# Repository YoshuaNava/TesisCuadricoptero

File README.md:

Estabilización de un cuadricoptero mediante un algoritmo Proporcional-Integral-Derivativo
==================

Documentos, códigos, imagenes y videos de la tesis. 

Trabajo realizado por Luis Vicens y Yoshua Nava, estudiantes de Ingeniería Informática de la Universidad Católica Andrés Bello.

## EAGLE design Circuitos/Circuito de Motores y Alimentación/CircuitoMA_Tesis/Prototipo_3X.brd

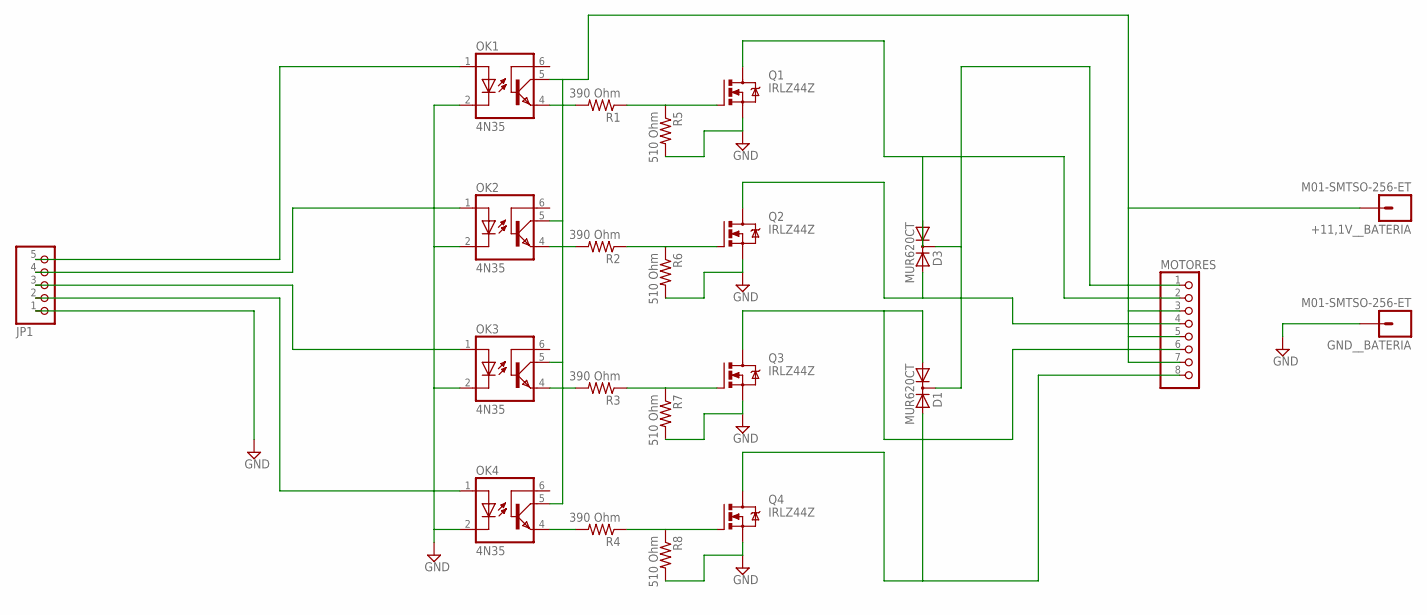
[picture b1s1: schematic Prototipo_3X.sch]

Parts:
+11,1V__BATERIA: M01-SMTSO-256-ET; SMTSO-256-ET
D1, D3: MUR620CT; TO220AB
GND__BATERIA: M01-SMTSO-256-ET; SMTSO-256-ET
JP1: PINHD-1X5/90; 1X05/90
MOTORES: PINHD-1X8/90; 1X08/90
OK1, OK2, OK3, OK4: 4N35; DIL06
Q1, Q2, Q3, Q4: IRLZ44Z; TO220BH
R1, R2, R3, R4: 390 Ohm; 0207/7
R5, R6, R7, R8: 510 Ohm; 0207/7

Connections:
GND: GND__BATERIA.P$1, JP1.1, OK1.2 (C), OK2.2 (C), OK3.2 (C), OK4.2 (C), Q1.S, Q2.S, Q3.S, Q4.S, R5.2, R6.2, R7.2, R8.2
unnamed: JP1.5, OK1.1 (A)
unnamed: JP1.4, OK2.1 (A)
unnamed: JP1.3, OK3.1 (A)
unnamed: JP1.2, OK4.1 (A)
unnamed: OK1.4 (EMI), R1.2
unnamed: Q1.G, R1.1, R5.1
unnamed: OK2.4 (EMI), R2.2
unnamed: OK3.4 (EMI), R3.2
unnamed: OK4.4 (EMI), R4.2
unnamed: Q4.G, R4.1, R8.1
unnamed: D3.A1, MOTORES.2, Q1.D
unnamed: Q3.G, R3.1, R7.1
unnamed: D3.A2, MOTORES.4, Q2.D
unnamed: D1.A1, MOTORES.6, Q3.D
unnamed: D1.A2, MOTORES.8, Q4.D
unnamed: Q2.G, R2.1, R6.1
unnamed: +11,1V__BATERIA.P$1, D1.C, D3.C, MOTORES.1, MOTORES.3, MOTORES.5, MOTORES.7, OK1.5 (COL), OK2.5 (COL), OK3.5 (COL), OK4.5 (COL)

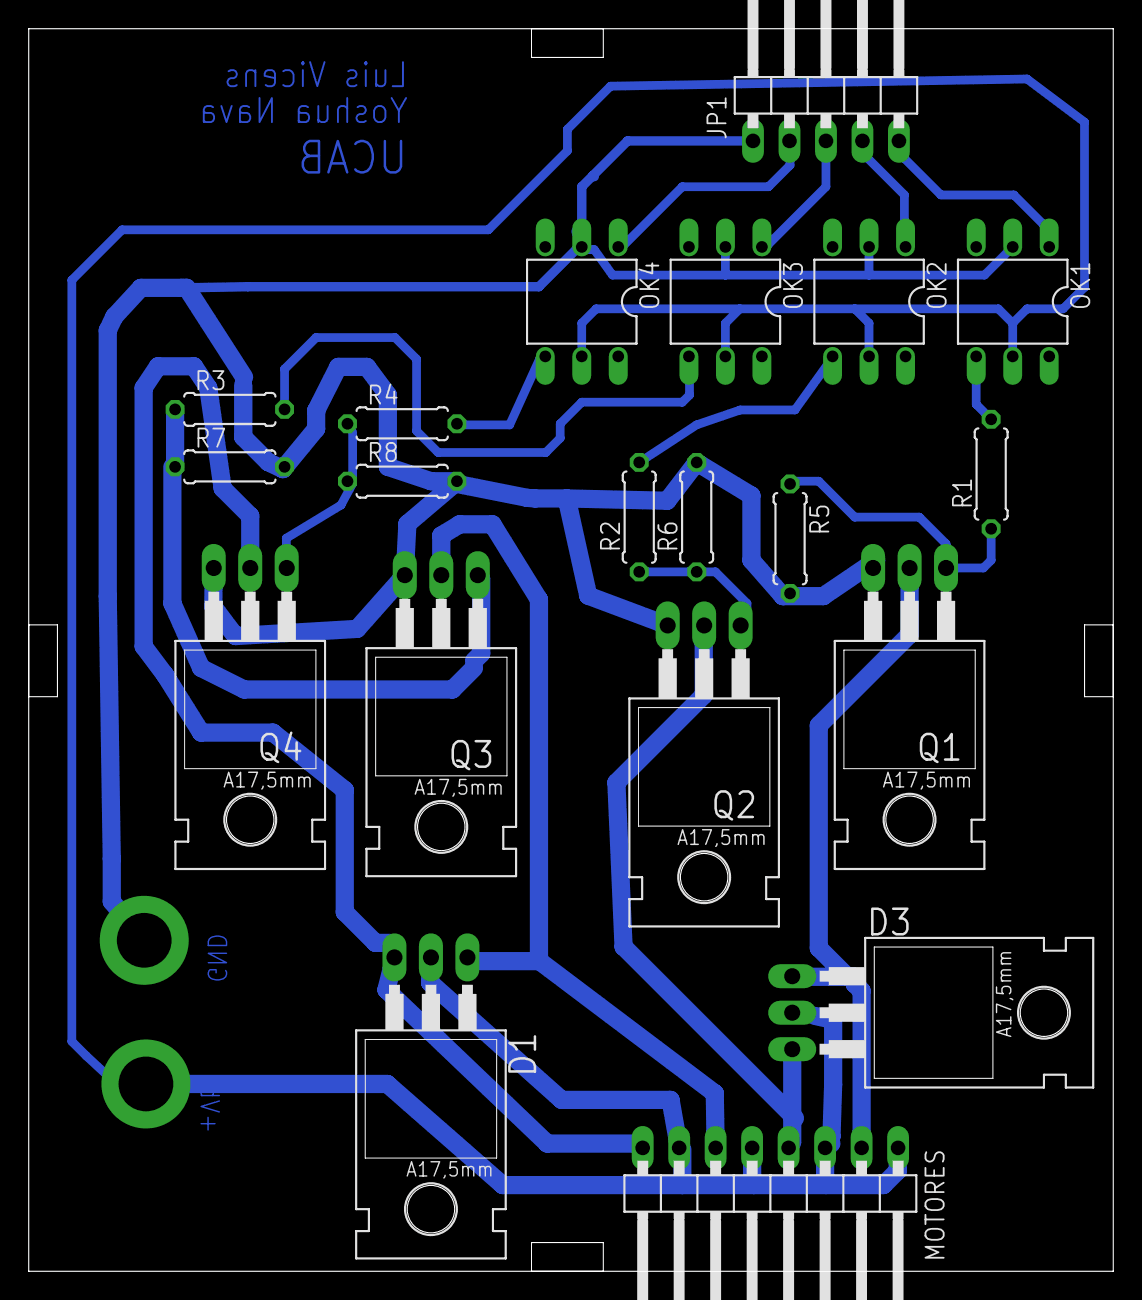
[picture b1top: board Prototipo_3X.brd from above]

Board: 2 copper layers, 75.5 x 86.5 mm, 22 parts (0 on the bottom side), 18 nets.

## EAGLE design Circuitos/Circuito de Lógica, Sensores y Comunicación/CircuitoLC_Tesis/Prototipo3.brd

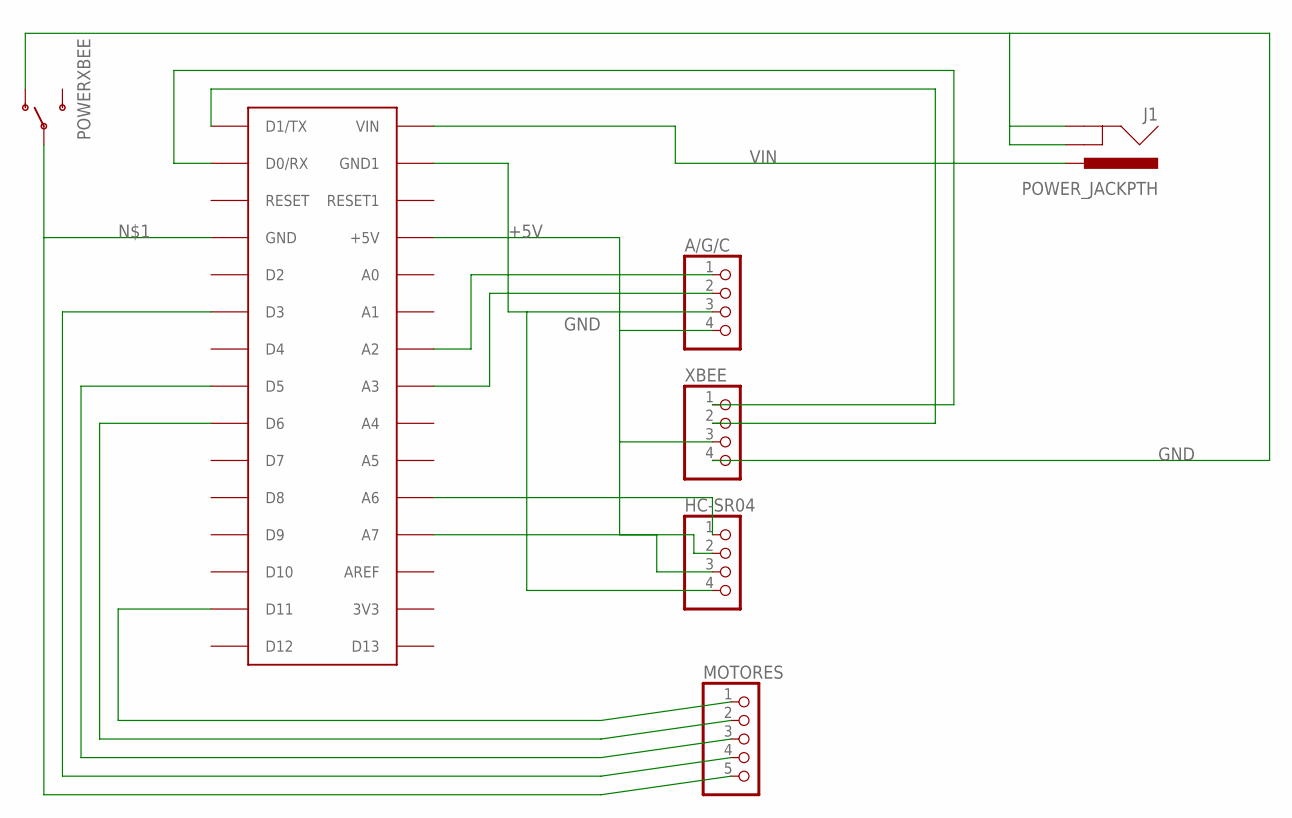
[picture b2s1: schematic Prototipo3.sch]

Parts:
A/G/C: PINHD-1X4/90; 1X04/90
HC-SR04: PINHD-1X4; 1X04
J1: POWER_JACKPTH; POWER_JACK_PTH
MOTORES: PINHD-1X5; 1X05
POWERXBEE: SWITCH-SPDTPTH; SWITCH-SPDT
U$1: ARDUINONANO; PDIP-32
XBEE: PINHD-1X4; 1X04

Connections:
+5V: A/G/C.4, HC-SR04.3, U$1.+5V, XBEE.3
GND: A/G/C.3, HC-SR04.4, J1.GND, J1.GNDBREAK, POWERXBEE.1 (O), U$1.GND1, XBEE.4
unnamed: MOTORES.5, POWERXBEE.2, U$1.GND
unnamed: MOTORES.4, U$1.D3
unnamed: MOTORES.3, U$1.D5
unnamed: MOTORES.2, U$1.D6
unnamed: MOTORES.1, U$1.D11
unnamed: HC-SR04.1, U$1.A6
unnamed: HC-SR04.2, U$1.A7
unnamed: A/G/C.1, U$1.A2
unnamed: A/G/C.2, U$1.A3
unnamed: U$1.D1/TX, XBEE.2
unnamed: U$1.D0/RX, XBEE.1
VIN: J1.PWR, U$1.VIN

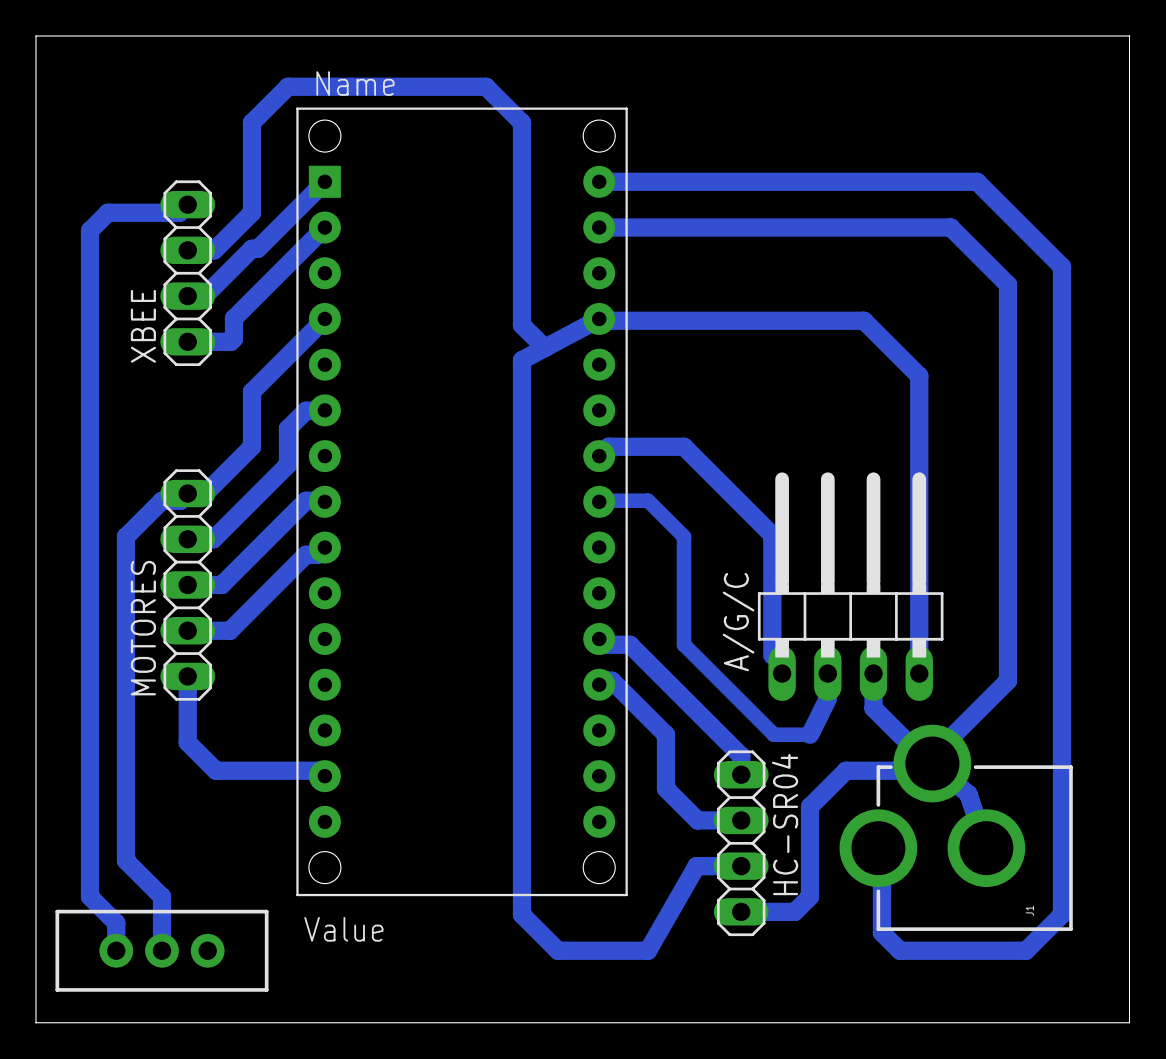
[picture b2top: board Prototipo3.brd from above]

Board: 2 copper layers, 60.8 x 54.8 mm, 7 parts (0 on the bottom side), 14 nets.

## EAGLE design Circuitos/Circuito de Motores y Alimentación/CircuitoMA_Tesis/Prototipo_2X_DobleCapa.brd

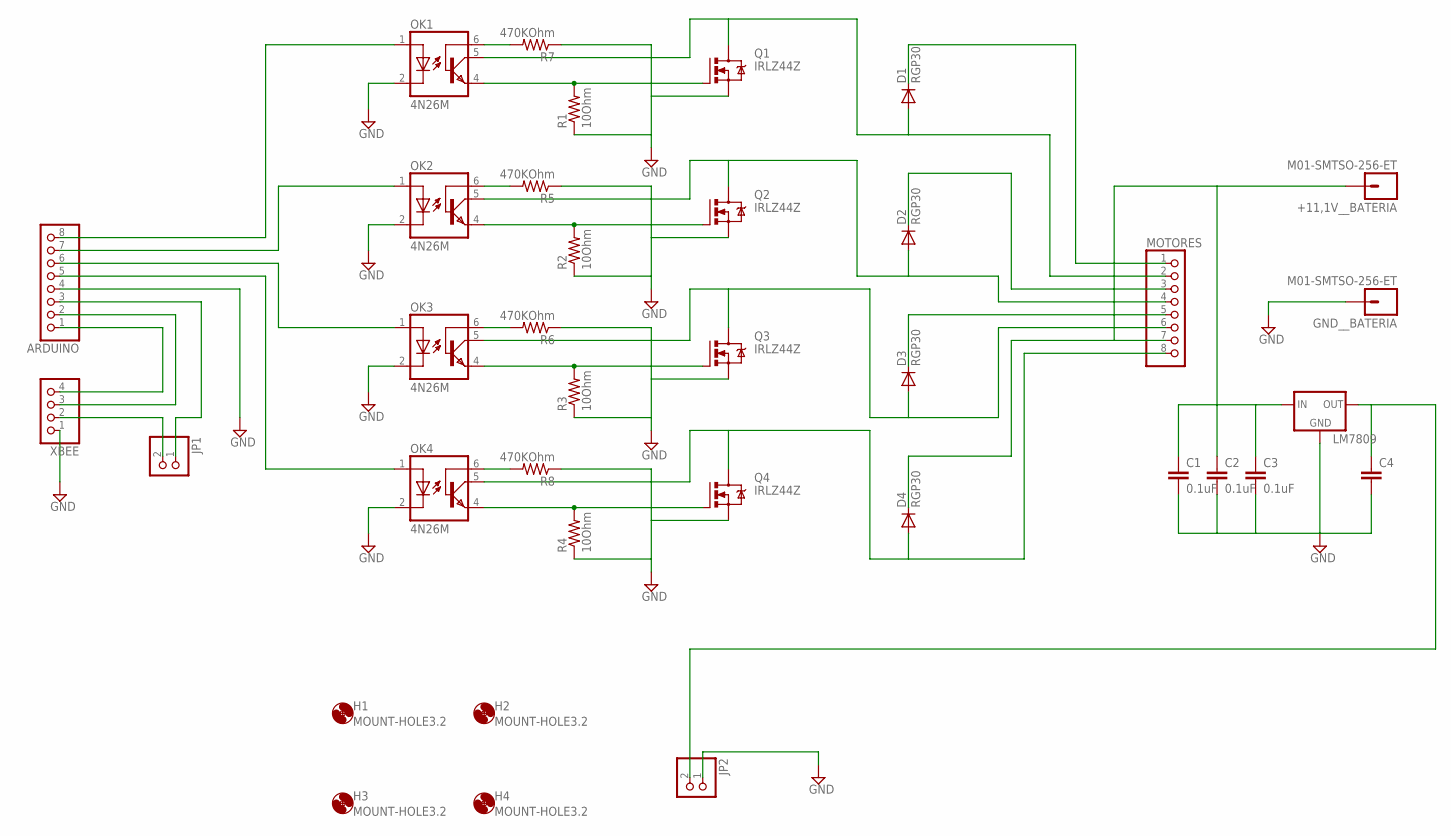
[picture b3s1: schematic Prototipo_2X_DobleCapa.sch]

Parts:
+11,1V__BATERIA: M01-SMTSO-256-ET; SMTSO-256-ET
ARDUINO: PINHD-1X8/90; 1X08/90
C1, C2, C3: 0.1uF; CAP-PTH-SMALL-KIT
C4: 0.1UF-50V-20%(PTH)KIT-EZ; CAP-PTH-SMALL-KIT
D1, D2, D3, D4: RGP30; DO201-15
GND__BATERIA: M01-SMTSO-256-ET; SMTSO-256-ET
H1, H2, H3, H4: MOUNT-HOLE3.2; 3,2
JP1: PINHD-1X2; 1X02
JP2: PINHD-1X2/90; 1X02/90
LM7809: 78XXL
MOTORES: PINHD-1X8/90; 1X08/90
OK1, OK2, OK3, OK4: 4N26M; DIL06
Q1, Q2, Q3, Q4: IRLZ44Z; TO220BH
R1, R2, R3, R4: 10Ohm; 0207/7
R5, R6, R7, R8: 470KOhm; 0207/7
XBEE: PINHD-1X4; 1X04

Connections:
GND: ARDUINO.4, C1.2, C2.2, C3.2, C4.2, GND__BATERIA.P$1, JP2.1, LM7809.GND, OK1.2 (C), OK2.2 (C), OK3.2 (C), OK4.2 (C), Q1.S, Q2.S, Q3.S, Q4.S, R1.1, R2.1, R3.1, R4.1, R5.1, R6.1, R7.1, R8.1, XBEE.1
unnamed: ARDUINO.8, OK1.1 (A)
unnamed: ARDUINO.7, OK2.1 (A)
unnamed: ARDUINO.6, OK3.1 (A)
unnamed: ARDUINO.5, OK4.1 (A)
unnamed: ARDUINO.1, XBEE.4
unnamed: OK1.6 (BAS), R7.2
unnamed: JP1.2, XBEE.2
unnamed: OK1.4 (EMI), Q1.G, R1.2
unnamed: OK2.4 (EMI), Q2.G, R2.2
unnamed: OK3.4 (EMI), Q3.G, R3.2
unnamed: OK4.4 (EMI), Q4.G, R4.2
unnamed: +11,1V__BATERIA.P$1, C1.1, C2.1, C3.1, D1.C, D2.C, D3.C, D4.C, LM7809.IN, MOTORES.1, MOTORES.3, MOTORES.5, MOTORES.7
unnamed: ARDUINO.2, XBEE.3
unnamed: D2.A, MOTORES.4, OK2.5 (COL), Q2.D
unnamed: D3.A, MOTORES.6, OK3.5 (COL), Q3.D
unnamed: D4.A, MOTORES.8, OK4.5 (COL), Q4.D
unnamed: D1.A, MOTORES.2, OK1.5 (COL), Q1.D
unnamed: C4.1, JP2.2, LM7809.OUT
unnamed: OK2.6 (BAS), R5.2
unnamed: ARDUINO.3, JP1.1
unnamed: OK3.6 (BAS), R6.2
unnamed: OK4.6 (BAS), R8.2

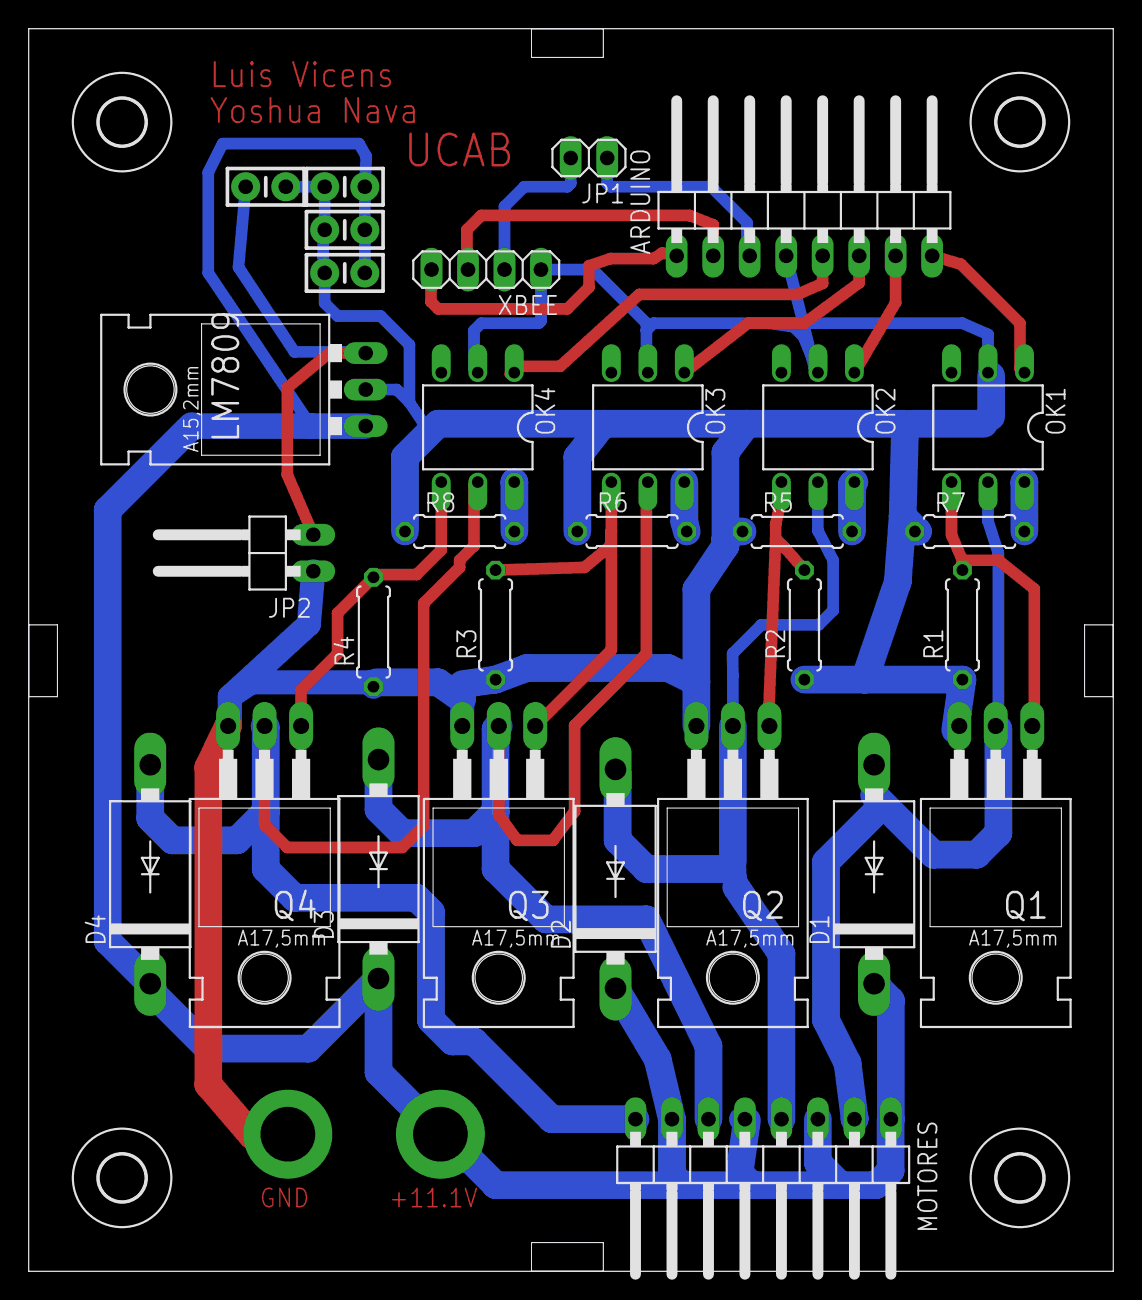
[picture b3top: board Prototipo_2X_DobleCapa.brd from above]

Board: 2 copper layers, 75.5 x 86.5 mm, 36 parts (0 on the bottom side), 23 nets.

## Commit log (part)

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2014-07-09 09/07/2014 00:56
2014-07-10 09/07/2014 20:24
2014-07-10 09/07/2014 23:11
2014-07-10 10/07/2014 01:59
2014-07-12 12/07/2014 00:02
    Calibración de los sistemas de control de velocidad y posición angular
2014-07-12 12/07/2014 02:40
2014-08-05 05/08/2014 02:09
2014-08-05 05/08/2014 02:24
2014-08-07 Interfaz en Qt
2014-08-08 Interfaz en Qt, y código para manejarla.
2014-08-08 Interfaz en Qt, manejando eventos y timer de ejecución.
2014-08-08 Interfaz en Qt con comentarios de TODO.
2014-08-08 Actualizacion del capitulo 2
    falta anadir filtro complementario al marco referencial
2014-08-11 Marco referencial
    Quité el filtro complementario, pues eso lo describiremos en el
    desarrollo del documento, justificando haberlo elegido en lugar de un
    filtro de Kalman simple.
2014-08-11 Lista de cosas por hacer
2014-08-11 Modulos de comunicacion Arduino/Python
    Queda por arreglar codigo de comandos y en python verificar que no este
    escuchando para poder enviar un comando
2014-08-11 Código para manejar el Joystick.
2014-08-11 Lista de cosas por hacer actualizada.
2014-08-11 Mejora modulo de comunicacion
    aun esta el problema desde python para recibir el ACK en el codigo de
    python
2014-08-14 Comunicación serial validada.
2014-08-14 Comunicación de Python con validaciones. Ya recibe bien los ACK de Arduino.
2014-08-19 Documento
    Añadido el índice del desarrollo de la tesis
2014-08-19 * Arduino: Ya se envia mensaje de estado a la PC. * Python: Ya hay un hilo escuchando el puerto serial, que se inicia con la ventana. El hilo en cuestion grafica con bastante retardo, y ademas, hay q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
2014-08-19 Lista de cosas por hacer.
2014-08-21 Código para pruebas de motores.
2014-08-26 comunicacion desarrollo y codigo en arduino
    Comunicacion en arduino se arreglo el mensaje de envio de etado, falta
    arreglarlo en python, se comenzo con la descripcion de la comunicacion
    para el desarrollo
2014-08-28 Documento
2014-09-01 Diagramas de circuitos viejos.
2014-09-04 Documento
    marco referencial arreglado listo para enviar a revision
2014-09-04 Archivos temporales del documento borrados
2014-09-04 Documento
    Filtro complementario listo.
2014-09-05 Circuitos y documento
    Circuito de control de motores.
2014-09-06 Documento
    Módulo de lógica, sensores y comunicación
2014-09-06 Documento
    Un poco del software, y descripción del sensor de altura utilizado.
2014-09-07 Circuito impreso
    Diseno del circuito impreso
2014-09-09 Circuito
    Aumentado el grosor de algunas pistas.
2014-09-09 Documento
    Detalles de presentación
2014-09-10 Desarrollo
2014-09-11 Documento
    Borrado documento viejo
2014-09-11 Reorganización del repositorio
2014-09-11 Documento
    Resultados y conclusiones
2014-09-11 Documento
    Planteamiento del problema
2014-09-11 Arduino - Envio de mensajes de estado. PC - Recepción de mensajes de estado
2014-09-12 Comunicacion.
2014-09-12 Comunicación lista.
2014-09-12 Arduino. Borrada una función que no estábamos utilizando.
2014-09-12 Arduino y Python.
2014-09-13 Arduino
    Reorganización del código.
2014-09-13 Arduino
2014-09-15 Filtro de Kalman de altura.
2014-09-15 Arduino: Filtro de Kalman de altura.
2014-09-15 Arduino: Calibracion de sistemas de control de posicion angular, velocidad angular y altura.
2014-09-16 Documento
    Conclusiones y desarrollo
2014-09-17 Documento
    Sistemas de control
2014-09-17 Documento
    Dedicatoria y agradecimientos.
2014-09-17 Referencia
    agregada referencia "Development and Implementation of a
    Control System for a quadrotor UAV"
2014-09-17 Documento
    Sistemas de control - Modelo/Simulación/Controlabilidad
2014-09-17 Modelo físico
2014-09-18 diagrama general de aplicacion y marco referencial
    se anadio filtro de kalman al marco reerencial
2014-09-18 Bibliografia actualizada
2014-09-18 Documento
    Desarrollo, marco referencial y conclusiones
2014-09-18 Documento
    Portada
2014-09-18 Documento
    Correcciones en el desarrollo
2014-09-18 Software, comunicación y giroscopio
2014-09-18 asdasd
2014-09-19 Software y Arduino
2014-09-19 Calibración Arduino.
2014-09-19 Calibración-Arduino.
2014-09-19 Calibración en Arduino.
2014-09-19 Sistema de control de altura.
2014-09-20 Software: Paquetes y mensajes de ROS.
2014-09-21 Software: Comunicacion ya recibe estado del cuadricóptero.
2014-09-21 Software: Nodo para el joystick Logitech Rumblepad II.
2014-09-21 Software listo!!! (El núcleo, capaz luego haya que hacer validaciones)
2014-09-21 Fotos y video en la carpeta principal. Tenemos demasiadas vibraciones al encender los motores .-.
2014-09-21 Removidos archivos viejos.
2014-09-21 Arduino: Filtro pasa-bajos de velocidad angular.
2014-09-21 Arduino: Corección en la implementación del filtro pasa-bajos.
2014-09-22 Desarrollo
    Mejorada:
    Plataforma de pruebas
    Comunicacion
    Falta hacer:
    SW de telemetria y comandos
2014-09-22 Arduino: Calibración.
2014-09-22 Arduino: Configuración del giroscopio.
2014-09-27 Filtro de Buterworth para velocidad YPR y acomodado offset
2014-09-27 butterworth+offset arreglado
2014-09-29 Documento
    Algunos detalles
2014-10-02 Documento
    Planteamiento del problema. Typo en el alcance.
    Desarrollo. Estimación de ángulo.
2014-10-06 Software: Exportador de mensajes de estado a formato CSV.
2014-10-06 Software: Organizacion del repositorio. Untrack de carpetas build y devel.
2014-10-06 Nuevo archivo .gitignore
2014-10-06 Linea de debugueo en el software.
2014-10-06 Análisis en frecuencia
2014-10-06 Análisis de respuesta en frecuencia de la IMU
2014-10-07 Scripts para analizar datos de la IMU en frecuencia.
2014-10-07 Scripts para realizar análisis de frecuencia.
2014-10-07 Scripts para realizar análisis en frecuencia de la IMU.
2014-10-09 graficas hechas aun falta centrar y poner limites
    se comentaron las lineas del AnalisisFReciencia para que el programa de
    graficas se encargara de hacer las graficas, recibe un vector de
    archivos [archivo1;archivo2] y la frecuencia
2014-10-11 Documento
    Resultados
2014-10-11 Documento
    Desarrollo y resultados
2014-10-11 Documentación y reorganización del repositorio
2014-10-13 Script para realizar analisis en frecuencia de la IMU y visualizar los resultados.
2014-10-13 cambio del programa principal de arduino a_angulo
2014-10-13 archivos de CSV para vibraciones
2014-10-14 Referencias.
2014-10-15 Arduino: Manejo de frecuencias de muestreo del acelerómetro y giroscopio.
2014-10-16 Arduino y analisis de respuesta en frecuencia.
2014-10-16 Arduino: Filtro de Kalman del acelerometro en Z.
2014-10-17 Nuevas pruebas de respuesta en frecuencia de la IMU, con amortiguación. Arduino: Filtros pasa bajos de 8Hz en el giroscopio y el acelerómetro. Manejo de frecuencia de muestreo rígido para mantener la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
2014-10-17 Comparación de modelo físico de otros trabajos con el DraganflyeV
2014-10-17 Arduino: Código para pruebas de calibración.
2014-10-17 Arduino: Código para análisis de respuesta en frecuencia de la IMU, y código para pruebas de calibración y vuelo del cuadricóptero.
2014-10-17 Calibración de PID de velocidad de Roll.
2014-10-17 Arduino: Comandos de velocidad en lugar de ángulo.
2014-10-18 Arduino: Control PID de velocidad angular solamente.
2014-10-18 Arduino: Control PID de velocidad solamente.
2014-10-18 Comparativa de modelos físicos. Eliminados archivos viejos del repositorio.
2014-10-19 Simulación del modelo físico.
2014-10-19 Simulación de PID de velocidad angular.
2014-10-19 Simulaciones de controladores de posición angular, velocidad angular, posición en Z y velocidad en Z.
2014-10-19 Desarrollo
    Desarrollo arreglos hecho por la tutora
2014-10-19 Documento: Conclusiones.
2014-10-20 Documento - Desarrollo:Sistemas de Control - Resultados. Diagramas.
2014-10-20 Simulación de los sistemas de control. Documento - Desarrollo: Sistemas de control.
2014-10-20 detalle arreglado en desarrollo y ROS y giroscopio arreglado en marco referencial
    se anadio una nuevareferencia y se arreglaron algunas cosas en
    conclusiones
2014-10-20 Documento - Desarrollo: Sistemas de control.
2014-10-22 Documento.
2014-10-22 Software: Implementacion de nuevo mensaje para telemetria total.
2014-10-22 Software y Arduino: Implementación del nuevo mensaje para telemetría.
2014-10-22 Borradas pruebas viejas de la IMU.
2014-10-23 desarrollo arreglado
2014-10-23 Arduino: Calibración de los sistemas de control.
2014-10-23 Calibración.
2014-10-24 Pruebas de rendimiento del PID de velocidad.
2014-10-24 MATLAB
2014-10-26 lista de graficas que faltan en el documento
2014-10-28 Modelo físico: Análisis de diagrama de fase (con errores)
2014-10-28 Análisis en fase de la dinámica del sistema.
2014-10-28 sdasd
2014-10-28 Arduino: Filtros.
2014-10-28 acelerometro y texto entre imagenes
2014-10-28 desarrollo diagramacion
2014-10-30 Documento
    Desarrollo, resultados y conclusiones
2014-11-01 Scripts de análisis de respuesta en frecuencia.
2014-11-01 fvtool
2014-11-02 Arduino y MATLAB.
2014-11-03 Estimación de posición angular aparentemente estable :O.
2014-11-03 Estimación de posición angular aparentemente estable O_O
2014-11-03 Arduino: Bug recibiendo comandos de posición angular.
2014-11-05 Arduino: Arquitectura mixta de control.
2014-11-05 Bug en el software.
2014-11-06 Arduino: Limpieza del código.
2014-11-07 Modelo y Arduino.
2014-11-07 Arduino: Calibración de PID de velocidad angular. Ahora se utilizan velocidades angulares filtradas en Pitch y Roll.
2014-11-18 matriz de tensores de inercia, arreglado
2014-11-20 Arreglo para telemetria total.
2014-11-20 paso de desarrollo a apendices
2014-11-20 Arduino con comentarios. Documento - Apendices y anexos. Portada y eso.
2014-11-20 Modelo fisico.
2014-11-23 Arduino: PID de velocidad en Z.
2014-11-24 Documento
    Desarrollo, ajustando un detalle.
2014-11-25 correcciones y consideracion de gravedad
2014-11-25 Documento
    Faltan diagramas y pruebas
2014-11-25 Diagramas, desarrollo y referencias
2014-11-26 Documentos.
2014-11-26 diagrama de estacion de control
2014-11-26 Cuadro de mensajes arreglado y referencia anadida al cuadro de velocidad de mensjaes
2014-11-26 imagenes xbee juntas desarrollo
2014-11-26 Documento. Falta lo de altura solamente.
2014-11-26 Paginas documento.
2014-11-27 Mejoras y diagrama de arduino anadido
2014-11-27 revisiones entrega anterior
2014-11-27 Documento a entregar para la tercera revisión.
2014-12-09 formato presentacion defensa TEG
2014-12-09 Arduino: posición angular y altura.
2015-01-01 Faltaba agregar el metodo para calcular Velocidad lineal en z.
2015-01-02 Documento. Apendices y anexos.
2015-01-05 Correcciones
    Errores ortograficos y de forma, Revisar
2015-01-06 Metodologia arreglado
    Descripcion de la metodolgia basada fundamentalmente en pressman,
    explicada paso a paso de forma generica y con el diagrama en espanol,
    creo que la referencia bibliogracia de Margaret Rouse ya no hace falta
    por facor revisar
2015-01-07 Union primer tomo, arreglos en desarrollo e indices
2015-01-08 Documento - Sinopsis.
2015-01-08 Documento - Introducción.
2015-01-08 Anexos con indice y primer tomo con indice arreglado
2015-01-09 Documento. Formato y reorganización de la carpeta.
2015-01-11 Metodologia
2015-01-12 Sólo faltan los números de las ecuaciones y mejorar la introducción.
2015-01-12 Sólo falta arreglar la introducción.
2015-01-12 Removiendo archivo temporal.
2015-01-12 NumeroPaginasDocumento.txt
2015-01-12 EntregaEntrega
2015-01-19 Archivos en PDF.
2015-01-24 Presentación.
2015-01-26 Diapositivas.
2015-01-27 Diapositivas
    Animaciones arregladas
2015-02-07 Documento - Diagrama general del sistema en otra posición.
2015-02-07 Tomo 2 - Glosario de términos.
2015-02-07 fuenes glosario pie de pagina
2015-02-12 MATLAB, scripts para analisis de rendimiento de los sistemas de control.

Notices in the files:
parts and their libraries:
SparkFun-Connectors: Licensing: Creative Commons ShareAlike 4.0 International - https://creativecommons.org/licenses/by-sa/4.0
